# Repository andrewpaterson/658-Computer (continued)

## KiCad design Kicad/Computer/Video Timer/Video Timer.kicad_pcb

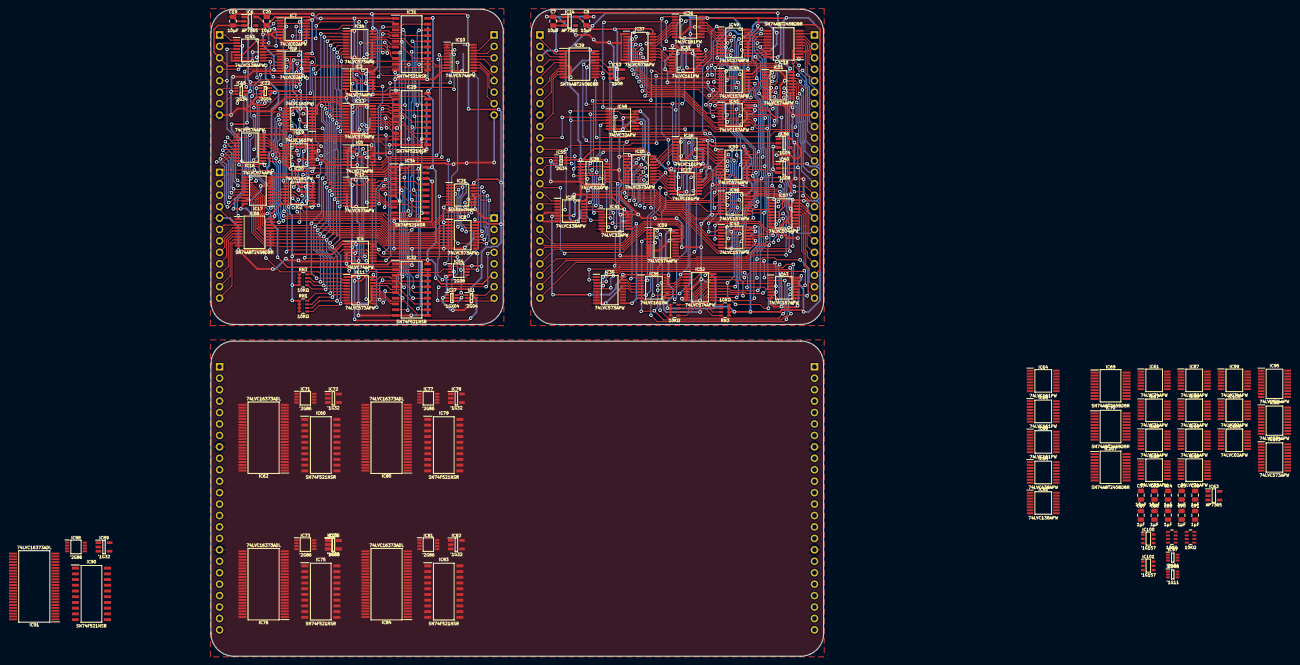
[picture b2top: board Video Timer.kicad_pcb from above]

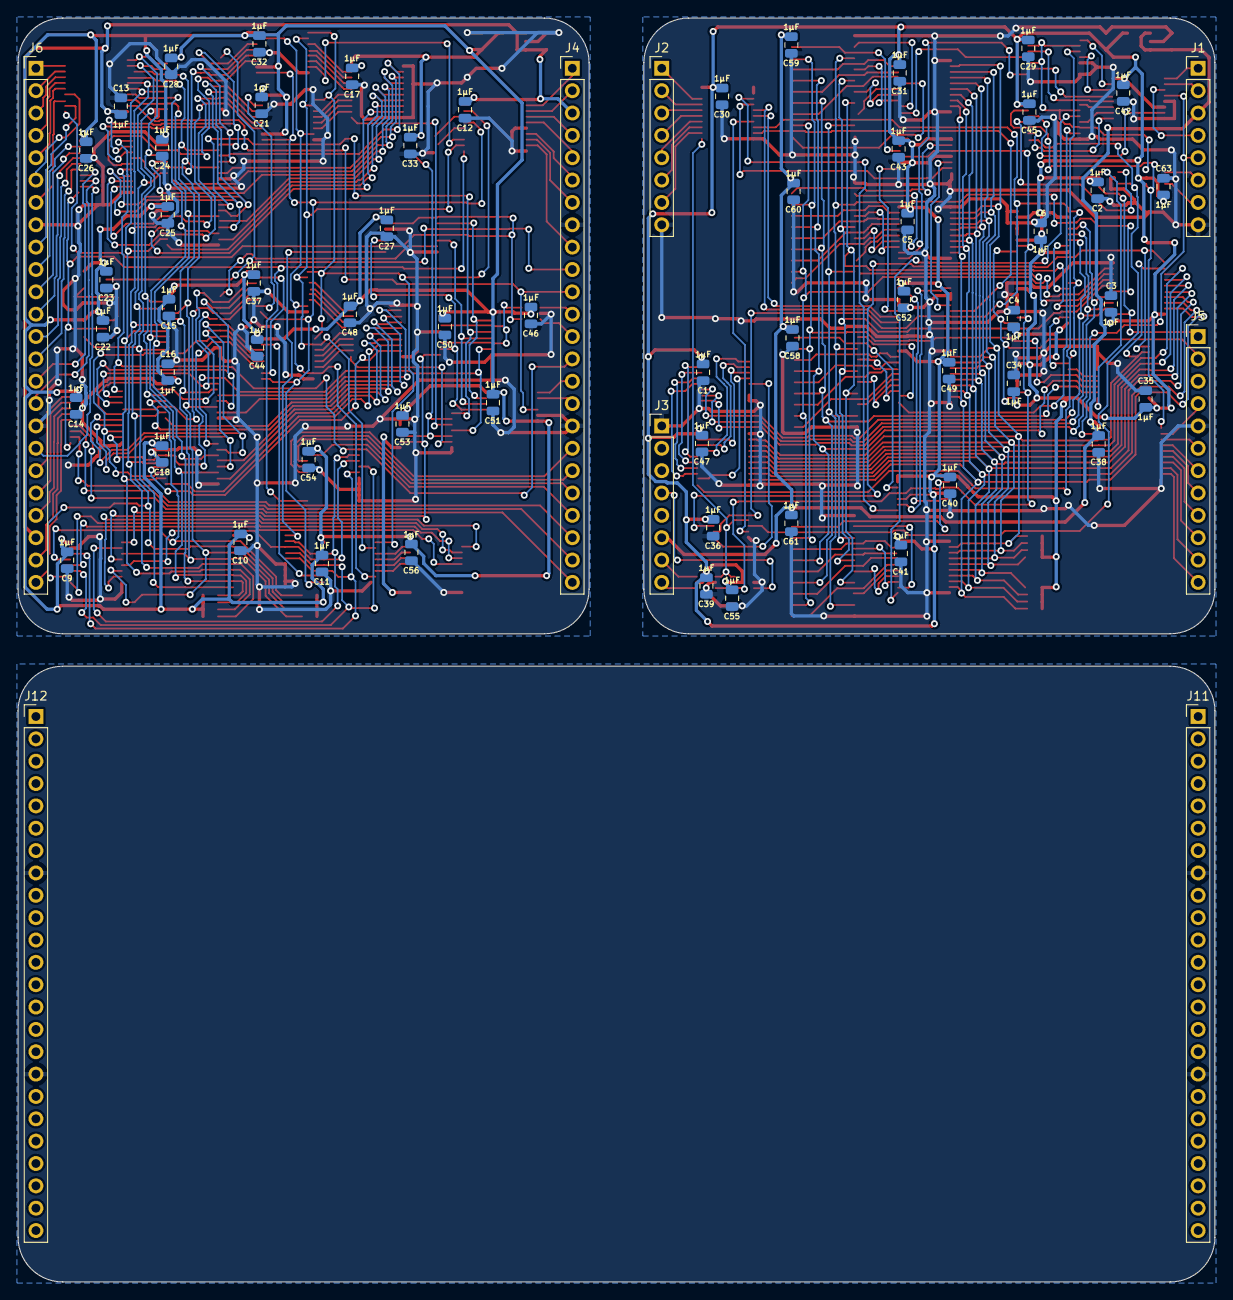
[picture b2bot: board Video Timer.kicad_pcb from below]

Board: 2 copper layers, 136.0 x 143.6 mm, 192 parts (65 on the bottom side), 433 nets.

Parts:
C1, C2, C3, C4, C5, C6, C9, C10, C11, C12, C13, C14, C15, C16, C17, C18, C21, C22, C23, C24, C25, C26, C27, C28, C29, C30, C31, C32, C33, C34, C35, C36, C37, C38, C39, C40, C41, C42, C43, C44, C45, C46, C47, C48, C49, C50, C51, C52, C53, C54, C55, C56, C58, C59, C60, C61, C63, C64, C65, C66, C67, C68, C69, C70, C71: 1μF; C_0805
C7, C8, C19, C20, C57, C62: 10µF; C_0805
IC1, IC22, IC97: 74LVC2G04GW-Q100H; SOP65P210X110-6N
IC2, IC19, IC20, IC23, IC26, IC33, IC35, IC36, IC64, IC65, IC66: 74LVC161PW,112; SOP65P640X110-16N
IC3, IC4, IC5, IC61, IC67, IC68, IC93, IC94, IC98, IC99: 74LVC74APW,118; SOP65P640X110-14N
IC6, IC24, IC63: AP7365-33WG-7; SOT95P285X130-5N
IC7, IC9, IC38, IC86, IC87, IC103, IC104: 74LVC02APW,118; SOP65P640X110-14N
IC8, IC11, IC12, IC13, IC14, IC25, IC30, IC37, IC102: 74LVC573APW,118; SOP65P640X110-20N
IC10, IC16, IC17, IC49, IC50, IC51, IC52, IC57, IC59, IC95, IC96: 74LVC574APW,118; SOP65P640X110-20N
IC15, IC55: 74LVC2G34GW,125; 74LVC2G34GW125
IC18, IC39, IC58, IC69, IC70, IC107: SN74ABT245BDBR; SOP65P780X200-20N
IC21: PI3B3251QE; SOP64P599X175-16N
IC27: 74LVC1GX04GW,125; SOP65P210X110-6N
IC28, IC42, IC85, IC92: 74LVC138APW-Q100J; SOP65P640X110-16N
IC29, IC31, IC32, IC34, IC60, IC75, IC79, IC83, IC90: SN74F521NSR; SOIC127P780X200-20N
IC40, IC53: 74LVC1G08GV,125; SOT95P275X110-5N
IC41, IC48: 74LVC32APW,118; SOP65P640X110-14N
IC43, IC44, IC45, IC46, IC47: 74LVC157APW,118; SOP65P640X110-16N
IC54: 74LVC2G08DP-Q100H; SOP65P400X110-8N
IC56, IC105: 74LVC1G04GV,125; SOT95P275X110-5N
IC62, IC76, IC80, IC84, IC91: 74LVC16373ADL,118; SOP64P1025X280-48N
IC71, IC73, IC77, IC81, IC88: 74LVC2G86DP,125; SOP65P400X110-8N
IC72, IC74, IC78, IC82, IC89: 74LVC1G32GV,125; SOT95P275X110-5N
IC100, IC101: 74LVC1G157GV,125; 74LVC1G157GV125
IC106: 74LVC1G11GW-Q100H; SOP65P210X110-6N
J1, J2, J3: Conn_01x08_Pin; PinHeader_1x08_P2.54mm_Vertical
J4, J6, J11, J12: Conn_01x24_Pin; PinHeader_1x24_P2.54mm_Vertical
J5: Conn_01x12_Pin; PinHeader_1x12_P2.54mm_Vertical
RN1, RN2, RN3, RN4, RN5, RN6: CAY16-103J4LF; CAY16-J4

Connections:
/Address Position/3.3V: C8.1, C9.1, C10.1, C11.1, C14.1, C15.1, C16.1, C17.1, C18.1, C21.1, C22.1, C23.1, C24.1, C25.1, C26.1, C27.1, C28.1, C32.1, C33.1, C37.1, C44.1, C46.1, C48.1, C50.1, C51.1, C53.1, C54.1, C56.1, IC23.16 (3V), IC24.5 (VOUT), IC25.20 (3V), IC26.16 (3V), IC28.6 (E3), IC28.16 (3V), IC30.20 (3V), IC33.10 (CET), IC33.16 (3V), IC35.16 (3V), IC36.10 (CET), IC36.16 (3V), IC37.20 (3V), IC38.14 (3V), IC40.5 (3V), IC41.14 (3V), IC43.16 (3V), IC44.16 (3V), IC45.16 (3V), IC46.16 (3V), IC47.16 (3V), IC48.14 (3V), IC49.20 (3V), IC50.20 (3V), IC51.20 (3V), IC52.20 (3V), IC53.5 (3V), IC55.5 (3V), IC56.5 (3V), IC57.20 (3V), IC59.20 (3V), RN3.5 (R4), RN3.6 (R3), RN3.7 (R2), RN3.8 (R1), RN4.5 (R4), RN4.6 (R3), RN4.7 (R2), RN4.8 (R1)
/Address Position/5V: C7.1, C12.1, C13.1, IC18.20 (5V), IC24.1 (VIN), IC24.3 (EN), IC39.1 (DIR), IC39.20 (5V), J4.3, J6.22
/Address Position/A0: IC28.1 (A0), J4.15
/Address Position/A1: IC28.2 (A1), J4.16
/Address Position/Address Bank ~CS: IC28.13 (~Y2), IC38.9 (3A), IC48.10 (3B)
/Address Position/Address High ~CS: IC28.14 (~Y1), IC38.4 (2A), IC48.5 (2B)
/Address Position/Address Low ~CS: IC28.15 (~Y0), IC38.1 (1A), IC48.2 (1B)
/Address Position/Advance Pixel: IC36.7 (CEP), IC39.13 (B6)
/Address Position/Advance Pixel _{IN}: IC39.7 (A6), J4.6
/Address Position/Advance Row: IC39.17 (B2), IC53.1 (B)
/Address Position/Advance Row _{IN}: IC39.3 (A2), J4.2
/Address Position/C0: IC36.14 (Q0), IC44.2 (1I0), IC49.2 (D0), IC51.2 (D0)
/Address Position/C1: IC36.13 (Q1), IC44.5 (2I0), IC49.3 (D1), IC51.3 (D1)
/Address Position/C2: IC36.12 (Q2), IC44.11 (3I0), IC49.4 (D2), IC51.4 (D2)
/Address Position/C3: IC36.11 (Q3), IC44.14 (4I0), IC49.5 (D3), IC51.5 (D3)
/Address Position/C4: IC33.14 (Q0), IC45.2 (1I0), IC49.6 (D4), IC51.6 (D4)
/Address Position/C5: IC33.13 (Q1), IC45.5 (2I0), IC49.7 (D5), IC51.7 (D5)
/Address Position/C6: IC33.12 (Q2), IC45.11 (3I0), IC49.8 (D6), IC51.8 (D6)
/Address Position/C7: IC33.11 (Q3), IC45.14 (4I0), IC49.9 (D7), IC51.9 (D7)
/Address Position/C8: IC26.14 (Q0), IC46.2 (1I0), IC50.2 (D0), IC57.2 (D0)
/Address Position/C9: IC26.13 (Q1), IC46.5 (2I0), IC50.3 (D1), IC57.3 (D1)
/Address Position/C10: IC26.12 (Q2), IC46.11 (3I0), IC50.4 (D2), IC57.4 (D2)
/Address Position/C11: IC26.11 (Q3), IC46.14 (4I0), IC50.5 (D3), IC57.5 (D3)
/Address Position/C12: IC23.14 (Q0), IC43.2 (1I0), IC50.6 (D4), IC57.6 (D4)
/Address Position/C13: IC23.13 (Q1), IC43.5 (2I0), IC50.7 (D5), IC57.7 (D5)
/Address Position/C14: IC23.12 (Q2), IC43.11 (3I0), IC50.8 (D6), IC57.8 (D6)
/Address Position/C15: IC23.11 (Q3), IC43.14 (4I0), IC50.9 (D7), IC57.9 (D7)
/Address Position/C16: IC35.14 (Q0), IC47.2 (1I0), IC52.2 (D0), IC59.2 (D0)
/Address Position/C17: IC35.13 (Q1), IC47.5 (2I0), IC52.3 (D1), IC59.3 (D1)
/Address Position/C18: IC35.12 (Q2), IC47.11 (3I0), IC52.4 (D2), IC59.4 (D2)
/Address Position/C19: IC35.11 (Q3), IC47.14 (4I0), IC52.5 (D3), IC59.5 (D3)
/Address Position/D0: IC18.11 (B8), IC44.13 (4I1), IC46.13 (4I1), IC47.13 (4I1), IC49.19 (Q0), IC50.19 (Q0), IC52.19 (Q0), RN4.4 (R4)
/Address Position/D0_{IN/OUT}: IC18.9 (A8), J6.1
/Address Position/D1: IC18.12 (B7), IC44.10 (3I1), IC46.10 (3I1), IC47.10 (3I1), IC49.18 (Q1), IC50.18 (Q1), IC52.18 (Q1), RN4.3 (R3)
/Address Position/D1_{IN/OUT}: IC18.8 (A7), J6.2
/Address Position/D2: IC18.13 (B6), IC44.6 (2I1), IC46.6 (2I1), IC47.6 (2I1), IC49.17 (Q2), IC50.17 (Q2), IC52.17 (Q2), RN4.2 (R2)
/Address Position/D2_{IN/OUT}: IC18.7 (A6), J6.3
/Address Position/D3: IC18.14 (B5), IC44.3 (1I1), IC46.3 (1I1), IC47.3 (1I1), IC49.16 (Q3), IC50.16 (Q3), IC52.16 (Q3), RN4.1 (R1)
/Address Position/D3_{IN/OUT}: IC18.6 (A5), J6.4
/Address Position/D4: IC18.15 (B4), IC43.13 (4I1), IC45.13 (4I1), IC49.15 (Q4), IC50.15 (Q4), IC52.15 (Q4), RN3.4 (R4)
/Address Position/D4_{IN/OUT}: IC18.5 (A4), J6.5
/Address Position/D5: IC18.16 (B3), IC43.10 (3I1), IC45.10 (3I1), IC49.14 (Q5), IC50.14 (Q5), IC52.14 (Q5), RN3.3 (R3)
/Address Position/D5_{IN/OUT}: IC18.4 (A3), J6.6
/Address Position/D6: IC18.17 (B2), IC43.6 (2I1), IC45.6 (2I1), IC49.13 (Q6), IC50.13 (Q6), IC52.13 (Q6), RN3.2 (R2)
/Address Position/D6_{IN/OUT}: IC18.3 (A2), J6.7
/Address Position/D7: IC18.18 (B1), IC43.3 (1I1), IC45.3 (1I1), IC49.12 (Q7), IC50.12 (Q7), IC52.12 (Q7), RN3.1 (R1)
/Address Position/D7_{IN/OUT}: IC18.2 (A1), J6.9
/Address Position/Device ~CS: IC18.19 (~OE), IC28.4 (~E1), J4.11
/Address Position/GA0: IC51.19 (Q0), J6.10
/Address Position/GA1: IC51.18 (Q1), J6.11
/Address Position/GA2: IC51.17 (Q2), J6.12
/Address Position/GA3: IC51.16 (Q3), J6.13
/Address Position/GA4: IC51.15 (Q4), J6.14
/Address Position/GA5: IC51.14 (Q5), J6.15
/Address Position/GA6: IC51.13 (Q6), J6.16
/Address Position/GA7: IC51.12 (Q7), J6.18
/Address Position/GA8: IC57.19 (Q0), J6.19
/Address Position/GA9: IC57.18 (Q1), J6.20
/Address Position/GA10: IC57.17 (Q2), J6.21
/Address Position/GA11: IC57.16 (Q3), J6.23
/Address Position/GA12: IC57.15 (Q4), J6.24
/Address Position/GA13: IC57.14 (Q5), J4.24
/Address Position/GA14: IC57.13 (Q6), J4.23
/Address Position/GA15: IC57.12 (Q7), J4.22
/Address Position/GA16: IC59.19 (Q0), J4.21
/Address Position/GA17: IC59.18 (Q1), J4.20
/Address Position/GA18: IC59.17 (Q2), J4.19
/Address Position/GA19: IC59.16 (Q3), J4.18
/Address Position/GND: C7.2, C8.2, C9.2, C10.2, C11.2, C12.2, C13.2, C14.2, C15.2, C16.2, C17.2, C18.2, C21.2, C22.2, C23.2, C24.2, C25.2, C26.2, C27.2, C28.2, C32.2, C33.2, C37.2, C44.2, C46.2, C48.2, C50.2, C51.2, C53.2, C54.2, C56.2, IC18.10 (GND), IC23.8 (GND), IC24.2 (GND), IC25.1 (~OE), IC25.10 (GND), IC26.8 (GND), IC28.3 (A2), IC28.5 (~E2), IC28.8 (GND), IC30.1 (~OE), IC30.6 (D4), IC30.7 (D5), IC30.8 (D6), IC30.9 (D7), IC30.10 (GND), IC33.8 (GND), IC35.8 (GND), IC36.8 (GND), IC37.1 (~OE), IC37.10 (GND), IC38.7 (GND), IC38.12 (4A), IC39.6 (A5), IC39.10 (GND), IC39.19 (~OE), IC40.3 (GND), IC41.7 (GND), IC41.12 (4A), IC41.13 (4B), IC43.8 (GND), IC43.15 (~E), IC44.8 (GND), IC44.15 (~E), IC45.8 (GND), IC45.15 (~E), IC46.8 (GND), IC46.15 (~E), IC47.8 (GND), IC47.15 (~E), IC48.7 (GND), IC48.12 (4A), IC49.10 (GND), IC50.10 (GND), IC51.10 (GND), IC52.6 (D4), IC52.7 (D5), IC52.8 (D6), IC52.9 (D7), IC52.10 (GND), IC53.3 (GND), IC55.2 (GND), IC56.3 (GND), IC57.10 (GND), IC59.6 (D4), IC59.7 (D5), IC59.8 (D6), IC59.9 (D7), IC59.10 (GND), J4.8, J4.17, J6.8, J6.17
/Address Position/Graphics Address ~OE: IC51.1 (~OE), IC57.1 (~OE), IC59.1 (~OE), J4.14
/Address Position/L0: IC37.2 (D0), IC44.4 (1Y)
/Address Position/L1: IC37.3 (D1), IC44.7 (2Y)
/Address Position/L2: IC37.4 (D2), IC44.9 (3Y)
/Address Position/L3: IC37.5 (D3), IC44.12 (4Y)
/Address Position/L4: IC37.6 (D4), IC45.4 (1Y)
/Address Position/L5: IC37.7 (D5), IC45.7 (2Y)
/Address Position/L6: IC37.8 (D6), IC45.9 (3Y)
/Address Position/L7: IC37.9 (D7), IC45.12 (4Y)
/Address Position/L8: IC25.2 (D0), IC46.4 (1Y)
/Address Position/L9: IC25.3 (D1), IC46.7 (2Y)
/Address Position/L10: IC25.4 (D2), IC46.9 (3Y)
/Address Position/L11: IC25.5 (D3), IC46.12 (4Y)
/Address Position/L12: IC25.6 (D4), IC43.4 (1Y)
/Address Position/L13: IC25.7 (D5), IC43.7 (2Y)
/Address Position/L14: IC25.8 (D6), IC43.9 (3Y)
/Address Position/L15: IC25.9 (D7), IC43.12 (4Y)
/Address Position/L16: IC30.2 (D0), IC47.4 (1Y)
/Address Position/L17: IC30.3 (D1), IC47.7 (2Y)
/Address Position/L18: IC30.4 (D2), IC47.9 (3Y)
/Address Position/L19: IC30.5 (D3), IC47.12 (4Y)
/Address Position/LC0: IC36.3 (D0), IC37.19 (Q0)
/Address Position/LC1: IC36.4 (D1), IC37.18 (Q1)
/Address Position/LC2: IC36.5 (D2), IC37.17 (Q2)
/Address Position/LC3: IC36.6 (D3), IC37.16 (Q3)
/Address Position/LC4: IC33.3 (D0), IC37.15 (Q4)
/Address Position/LC5: IC33.4 (D1), IC37.14 (Q5)
/Address Position/LC6: IC33.5 (D2), IC37.13 (Q6)
/Address Position/LC7: IC33.6 (D3), IC37.12 (Q7)
/Address Position/LC8: IC25.19 (Q0), IC26.3 (D0)
/Address Position/LC9: IC25.18 (Q1), IC26.4 (D1)
/Address Position/LC10: IC25.17 (Q2), IC26.5 (D2)
/Address Position/LC11: IC25.16 (Q3), IC26.6 (D3)
/Address Position/LC12: IC23.3 (D0), IC25.15 (Q4)
/Address Position/LC13: IC23.4 (D1), IC25.14 (Q5)
/Address Position/LC14: IC23.5 (D2), IC25.13 (Q6)
/Address Position/LC15: IC23.6 (D3), IC25.12 (Q7)
/Address Position/LC16: IC30.19 (Q0), IC35.3 (D0)
/Address Position/LC17: IC30.18 (Q1), IC35.4 (D1)
/Address Position/LC18: IC30.17 (Q2), IC35.5 (D2)
/Address Position/LC19: IC30.16 (Q3), IC35.6 (D3)
/Address Position/LP·AR: IC41.2 (1B), IC41.5 (2B), IC41.10 (3B), IC53.4 (Y)
/Address Position/Last Pixel + 1: IC39.15 (B4), IC53.2 (A)
/Address Position/Last Pixel + 1 _{IN}: IC39.5 (A4), J4.5
/Address Position/Latch Bank: IC30.11 (LE), IC41.8 (3Y)
/Address Position/Latch High: IC25.11 (LE), IC41.6 (2Y)
/Address Position/Latch Low: IC37.11 (LE), IC41.3 (1Y)
/Address Position/Pixel CLK: IC23.2 (CP), IC26.2 (CP), IC33.2 (CP), IC35.2 (CP), IC36.2 (CP), IC39.12 (B7)
/Address Position/Pixel CLK _{IN}: IC39.8 (A7), J4.7
/Address Position/Read Address Low: IC40.1 (B), IC56.4 (Y)
/Address Position/TC_{0..3}: IC23.7 (CEP), IC26.7 (CEP), IC33.7 (CEP), IC35.7 (CEP), IC36.15 (TC)
/Address Position/TC_{4..7}: IC26.10 (CET), IC33.15 (TC)
/Address Position/TC_{8..11}: IC23.10 (CET), IC26.15 (TC)
/Address Position/TC_{12..15}: IC23.15 (TC), IC35.10 (CET)
/Address Position/Write Address Bank: IC38.8 (3Y), IC41.9 (3A), IC47.1 (S)
/Address Position/Write Address High: IC38.6 (2Y), IC41.4 (2A), IC43.1 (S), IC46.1 (S)
/Address Position/Write Address Low: IC38.3 (1Y), IC41.1 (1A), IC44.1 (S), IC45.1 (S)
/Address Position/~Horizontal Blank: IC23.9 (~PE), IC26.9 (~PE), IC33.9 (~PE), IC35.9 (~PE), IC36.9 (~PE), IC39.16 (B3)
/Address Position/~Horizontal Blank _{IN}: IC39.4 (A3), J4.4
/Address Position/~PC·RAL: IC40.4 (Y), IC49.11 (CP), IC50.11 (CP), IC52.11 (CP)
/Address Position/~Pixel CLK: IC39.11 (B8), IC40.2 (A), IC51.11 (CP), IC57.11 (CP), IC59.11 (CP)
/Address Position/~Pixel CLK _{IN}: IC39.9 (A8), J4.9
/Address Position/~RD: IC18.1 (DIR), IC48.1 (1A), IC48.4 (2A), IC48.9 (3A), IC48.13 (4B), IC55.4 (2Y)
/Address Position/~RD_{IN}: IC55.3 (2A), J4.13
/Address Position/~Read Address Bank: IC48.8 (3Y), IC52.1 (~OE)
/Address Position/~Read Address High: IC48.6 (2Y), IC50.1 (~OE)
/Address Position/~Read Address Low: IC48.3 (1Y), IC49.1 (~OE), IC56.2 (A), J4.10
/Address Position/~Reset: IC23.1 (~MR), IC26.1 (~MR), IC33.1 (~MR), IC35.1 (~MR), IC36.1 (~MR), IC39.18 (B1)
/Address Position/~Reset _{IN}: IC39.2 (A1), J4.1
/Address Position/~WD: IC38.2 (1B), IC38.5 (2B), IC38.10 (3B), IC38.13 (4B), IC55.6 (1Y)
/Address Position/~WD_{IN}: IC55.1 (1A), J4.12
/Horizontal Position/3.3V: C1.1, C2.1, C3.1, C4.1, C5.1, C6.1, C20.1, C29.1, C30.1, C31.1, C34.1, C35.1, C36.1, C39.1, C40.1, C41.1, C42.1, C43.1, C45.1, C47.1, C49.1, C52.1, C55.1, C63.1, IC1.5 (3V), IC2.7 (CEP), IC2.16 (3V), IC3.1 (~1RD), IC3.4 (~1SD), IC3.10 (~2SD), IC3.13 (~2RD), IC3.14 (3V), IC4.1 (~1RD), IC4.4 (~1SD), IC4.10 (~2SD), IC4.13 (~2RD), IC4.14 (3V), IC5.14 (3V), IC6.5 (VOUT), IC7.14 (3V), IC8.20 (3V), IC9.14 (3V), IC10.20 (3V), IC11.20 (3V), IC12.20 (3V), IC13.20 (3V), IC14.20 (3V), IC15.5 (3V), IC16.20 (3V), IC17.20 (3V), IC19.3 (D0), IC19.7 (CEP), IC19.10 (CET), IC19.16 (3V), IC20.7 (CEP), IC20.16 (3V), IC21.16 (3V), IC22.5 (3V), IC27.5 (3V), IC42.6 (E3), IC42.16 (3V), IC54.8 (3V), RN1.5 (R4), RN1.6 (R3), RN1.7 (R2), RN1.8 (R1), RN2.5 (R4), RN2.6 (R3), RN2.7 (R2), RN2.8 (R1)
/Horizontal Position/5V: C19.1, C38.1, C58.1, C59.1, C60.1, C61.1, IC6.1 (VIN), IC6.3 (EN), IC29.20 (5V), IC31.20 (5V), IC32.20 (5V), IC34.20 (5V), IC58.20 (5V), J1.3, J3.6
/Horizontal Position/A0: IC42.1 (A0), J1.1
/Horizontal Position/A1: IC42.2 (A1), J1.2
/Horizontal Position/A2: IC42.3 (A2), J1.4
/Horizontal Position/Advance Pixel: IC10.7 (D5), IC54.3 (2Y)
/Horizontal Position/Advance Pixel _{OUT}: IC10.14 (Q5), J2.5
/Horizontal Position/Back Porch End D0: IC12.12 (Q7), IC34.2 (P0)
/Horizontal Position/Back Porch End D1: IC12.13 (Q6), IC34.4 (P1)
/Horizontal Position/Back Porch End D2: IC12.14 (Q5), IC34.6 (P2)
/Horizontal Position/Back Porch End D3: IC12.15 (Q4), IC34.8 (P3)
/Horizontal Position/Back Porch End D4: IC12.16 (Q3), IC34.11 (P4)
/Horizontal Position/Back Porch End D5: IC12.17 (Q2), IC34.13 (P5)
/Horizontal Position/Back Porch End D6: IC12.18 (Q1), IC34.15 (P6)
/Horizontal Position/Back Porch End D7: IC12.19 (Q0), IC34.17 (P7)
/Horizontal Position/Back Porch Start D0: IC11.12 (Q7), IC32.2 (P0)
/Horizontal Position/Back Porch Start D1: IC11.13 (Q6), IC32.4 (P1)
/Horizontal Position/Back Porch Start D2: IC11.14 (Q5), IC32.6 (P2)
/Horizontal Position/Back Porch Start D3: IC11.15 (Q4), IC32.8 (P3)
/Horizontal Position/Back Porch Start D4: IC11.16 (Q3), IC32.11 (P4)
/Horizontal Position/Back Porch Start D5: IC11.17 (Q2), IC32.13 (P5)
/Horizontal Position/Back Porch Start D6: IC11.18 (Q1), IC32.15 (P6)
/Horizontal Position/Back Porch Start D7: IC11.19 (Q0), IC32.17 (P7)
/Horizontal Position/Clock Read Row Position: IC16.11 (CP), IC17.11 (CP), IC54.7 (1Y)
/Horizontal Position/D0: IC8.9 (D7), IC11.9 (D7), IC12.9 (D7), IC13.9 (D7), IC14.9 (D7), IC16.19 (Q0), IC17.19 (Q0), IC58.11 (B8), RN1.1 (R1)
/Horizontal Position/D0_{IN/OUT}: IC58.9 (A8), J5.12
/Horizontal Position/D1: IC8.8 (D6), IC11.8 (D6), IC12.8 (D6), IC13.8 (D6), IC14.8 (D6), IC16.18 (Q1), IC17.18 (Q1), IC58.12 (B7), RN1.2 (R2)
/Horizontal Position/D1_{IN/OUT}: IC58.8 (A7), J5.11
/Horizontal Position/D2: IC8.7 (D5), IC11.7 (D5), IC12.7 (D5), IC13.7 (D5), IC14.7 (D5), IC16.17 (Q2), IC17.17 (Q2), IC58.13 (B6), RN1.3 (R3)
/Horizontal Position/D2_{IN/OUT}: IC58.7 (A6), J5.10
/Horizontal Position/D3: IC8.6 (D4), IC11.6 (D4), IC12.6 (D4), IC13.6 (D4), IC14.6 (D4), IC16.16 (Q3), IC17.16 (Q3), IC58.14 (B5), RN1.4 (R4)
/Horizontal Position/D3_{IN/OUT}: IC58.6 (A5), J5.9
/Horizontal Position/D4: IC8.5 (D3), IC11.5 (D3), IC12.5 (D3), IC13.5 (D3), IC14.5 (D3), IC16.15 (Q4), IC17.15 (Q4), IC58.15 (B4), RN2.1 (R1)
/Horizontal Position/D4_{IN/OUT}: IC58.5 (A4), J5.8
/Horizontal Position/D5: IC8.4 (D2), IC11.4 (D2), IC12.4 (D2), IC13.4 (D2), IC14.4 (D2), IC16.14 (Q5), IC17.14 (Q5), IC58.16 (B3), RN2.2 (R2)
/Horizontal Position/D5_{IN/OUT}: IC58.4 (A3), J5.7
/Horizontal Position/D6: IC8.3 (D1), IC11.3 (D1), IC12.3 (D1), IC13.3 (D1), IC14.3 (D1), IC16.13 (Q6), IC17.13 (Q6), IC58.17 (B2), RN2.3 (R3)
/Horizontal Position/D6_{IN/OUT}: IC58.3 (A2), J5.6
/Horizontal Position/D7: IC8.2 (D0), IC11.2 (D0), IC12.2 (D0), IC13.2 (D0), IC14.2 (D0), IC16.12 (Q7), IC17.12 (Q7), IC58.18 (B1), RN2.4 (R4)
/Horizontal Position/D7_{IN/OUT}: IC58.2 (A1), J5.4
/Horizontal Position/Device ~CS: IC42.4 (~E1), IC58.19 (~OE), J1.5
/Horizontal Position/First Pixel: IC4.8 (~2Q), IC10.3 (D1)
/Horizontal Position/First Pixel _{OUT}: IC10.18 (Q1), J2.1
/Horizontal Position/Front Porch Start D0: IC13.12 (Q7), IC29.2 (P0)
/Horizontal Position/Front Porch Start D1: IC13.13 (Q6), IC29.4 (P1)
/Horizontal Position/Front Porch Start D2: IC13.14 (Q5), IC29.6 (P2)
/Horizontal Position/Front Porch Start D3: IC13.15 (Q4), IC29.8 (P3)
/Horizontal Position/Front Porch Start D4: IC13.16 (Q3), IC29.11 (P4)
/Horizontal Position/Front Porch Start D5: IC13.17 (Q2), IC29.13 (P5)
/Horizontal Position/Front Porch Start D6: IC13.18 (Q1), IC29.15 (P6)
/Horizontal Position/Front Porch Start D7: IC13.19 (Q0), IC29.17 (P7)
/Horizontal Position/GND: C1.2, C2.2, C3.2, C4.2, C5.2, C6.2, C19.2, C20.2, C29.2, C30.2, C31.2, C34.2, C35.2, C36.2, C38.2, C39.2, C40.2, C41.2, C42.2, C43.2, C45.2, C47.2, C49.2, C52.2, C55.2, C58.2, C59.2, C60.2, C61.2, C63.2, IC1.2 (GND), IC2.3 (D0), IC2.4 (D1), IC2.5 (D2), IC2.6 (D3), IC2.8 (GND), IC3.7 (GND), IC4.7 (GND), IC5.2 (1D), IC5.3 (1CP), IC5.7 (GND), IC5.11 (2CP), IC5.12 (2D), IC6.2 (GND), IC7.5 (2B), IC7.7 (GND), IC8.1 (~OE), IC8.10 (GND), IC9.7 (GND), IC10.1 (~OE), IC10.2 (D0), IC10.10 (GND), IC11.1 (~OE), IC11.10 (GND), IC12.1 (~OE), IC12.10 (GND), IC13.1 (~OE), IC13.10 (GND), IC14.1 (~OE), IC14.10 (GND), IC15.2 (GND), IC16.10 (GND), IC17.6 (D4), IC17.7 (D5), IC17.8 (D6), IC17.9 (D7), IC17.10 (GND), IC19.4 (D1), IC19.5 (D2), IC19.6 (D3), IC19.8 (GND), IC20.3 (D0), IC20.4 (D1), IC20.5 (D2), IC20.6 (D3), IC20.8 (GND), IC21.7 (~OE), IC21.8 (GND), IC22.2 (GND), IC27.2 (GND), IC29.1 (~OE), IC29.10 (GND), IC31.1 (~OE), IC31.10 (GND), IC32.1 (~OE), IC32.10 (GND), IC34.1 (~OE), IC34.10 (GND), IC42.5 (~E2), IC42.8 (GND), IC54.4 (GND), IC58.10 (GND), J1.8, J2.8, J3.1, J5.5
/Horizontal Position/Horizontal Blank: IC5.5 (1Q), IC10.9 (D7)
/Horizontal Position/Horizontal Blank _{OUT}: IC10.12 (Q7), J2.7
/Horizontal Position/Horizontal Sync: IC5.9 (2Q), IC10.6 (D4)
/Horizontal Position/Horizontal Sync _{OUT}: IC10.15 (Q4), J2.4
/Horizontal Position/Last Pixel + 1: IC3.6 (~1Q), IC10.4 (D2)
/Horizontal Position/Last Pixel + 1 _{OUT}: IC10.17 (Q2), J2.2
/Horizontal Position/Pixel CLK: IC1.3 (2A), IC2.2 (CP), IC3.3 (1CP), IC3.11 (2CP), IC4.3 (1CP), IC4.11 (2CP), IC19.2 (CP), IC20.2 (CP), IC27.4 (~Y)
/Horizontal Position/Pixel CLK _{IN}: IC27.3 (X1), J3.4
/Horizontal Position/Pixel CLK _{OUT}: IC1.6 (1Y), J3.7
/Horizontal Position/R0: IC16.2 (D0), IC19.14 (Q0), IC21.11 (S0)
/Horizontal Position/R1: IC16.3 (D1), IC19.13 (Q1), IC21.10 (S1)
/Horizontal Position/R2: IC16.4 (D2), IC19.12 (Q2), IC21.9 (S2)
/Horizontal Position/R3: IC16.5 (D3), IC19.11 (Q3), IC29.3 (Q0), IC31.3 (Q0), IC32.3 (Q0), IC34.3 (Q0)
/Horizontal Position/R4: IC16.6 (D4), IC20.14 (Q0), IC29.5 (Q1), IC31.5 (Q1), IC32.5 (Q1), IC34.5 (Q1)
/Horizontal Position/R5: IC16.7 (D5), IC20.13 (Q1), IC29.7 (Q2), IC31.7 (Q2), IC32.7 (Q2), IC34.7 (Q2)
/Horizontal Position/R6: IC16.8 (D6), IC20.12 (Q2), IC29.9 (Q3), IC31.9 (Q3), IC32.9 (Q3), IC34.9 (Q3)
/Horizontal Position/R7: IC16.9 (D7), IC20.11 (Q3), IC29.12 (Q4), IC31.12 (Q4), IC32.12 (Q4), IC34.12 (Q4)
/Horizontal Position/R8: IC2.14 (Q0), IC17.2 (D0), IC29.14 (Q5), IC31.14 (Q5), IC32.14 (Q5), IC34.14 (Q5)
/Horizontal Position/R9: IC2.13 (Q1), IC17.3 (D1), IC29.16 (Q6), IC31.16 (Q6), IC32.16 (Q6), IC34.16 (Q6)
/Horizontal Position/R10: IC2.12 (Q2), IC17.4 (D2), IC29.18 (Q7), IC31.18 (Q7), IC32.18 (Q7), IC34.18 (Q7)
/Horizontal Position/R11: IC2.11 (Q3), IC17.5 (D3)
/Horizontal Position/RPS0: IC8.19 (Q0), IC21.3 (I1)
/Horizontal Position/RPS1: IC8.18 (Q1), IC21.2 (I2)
/Horizontal Position/RPS2: IC8.17 (Q2), IC21.1 (I3)
/Horizontal Position/RPS3: IC8.16 (Q3), IC21.15 (I4)
/Horizontal Position/RPS4: IC8.15 (Q4), IC21.14 (I5)
/Horizontal Position/RPS5: IC8.14 (Q5), IC21.13 (I6)
/Horizontal Position/RPS6: IC8.13 (Q6), IC21.12 (I7)
/Horizontal Position/RPS7: IC8.12 (Q7), IC21.4 (I0)
/Horizontal Position/Read Row Position High: IC9.11 (4Y), IC22.1 (1A)
/Horizontal Position/Read Row Position High ~CS: IC9.12 (4A), IC42.7 (~Y7)
/Horizontal Position/Read Row Position Low: IC9.8 (3Y), IC22.3 (2A), IC54.2 (1B)
/Horizontal Position/Read Row Position Low ~CS: IC9.9 (3A), IC42.9 (~Y6)
/Horizontal Position/Select Advance Pixel: IC21.5 (Y), IC54.5 (2A)
/Horizontal Position/Sync Start D0: IC14.12 (Q7), IC31.2 (P0)
/Horizontal Position/Sync Start D1: IC14.13 (Q6), IC31.4 (P1)
/Horizontal Position/Sync Start D2: IC14.14 (Q5), IC31.6 (P2)
/Horizontal Position/Sync Start D3: IC14.15 (Q4), IC31.8 (P3)
/Horizontal Position/Sync Start D4: IC14.16 (Q3), IC31.11 (P4)
/Horizontal Position/Sync Start D5: IC14.17 (Q2), IC31.13 (P5)
/Horizontal Position/Sync Start D6: IC14.18 (Q1), IC31.15 (P6)
/Horizontal Position/Sync Start D7: IC14.19 (Q0), IC31.17 (P7)
/Horizontal Position/TC_{0123}: IC19.15 (TC), IC20.10 (CET)
/Horizontal Position/TC_{4567}: IC2.10 (CET), IC20.15 (TC)
/Horizontal Position/Write Back Porch End: IC9.6 (2Y), IC12.11 (LE)
/Horizontal Position/Write Back Porch End ~CS: IC9.4 (2A), IC42.10 (~Y5)
/Horizontal Position/Write Back Porch Start: IC9.3 (1Y), IC11.11 (LE)
/Horizontal Position/Write Back Porch Start ~CS: IC9.1 (1A), IC42.11 (~Y4)
/Horizontal Position/Write Front Porch Start: IC7.8 (3Y), IC13.11 (LE)
/Horizontal Position/Write Front Porch Start ~CS: IC7.9 (3A), IC42.13 (~Y2)
/Horizontal Position/Write Shift Pattern: IC7.3 (1Y), IC8.11 (LE)
/Horizontal Position/Write Shift Pattern ~CS: IC7.1 (1A), IC42.15 (~Y0)
/Horizontal Position/Write Sync Start: IC7.11 (4Y), IC14.11 (LE)
/Horizontal Position/Write Sync Start ~CS: IC7.12 (4A), IC42.12 (~Y3)
/Horizontal Position/~Back Porch End: IC4.9 (2Q), IC5.1 (~1RD)
/Horizontal Position/~Back Porch End _{CMP}: IC4.12 (2D), IC34.19 (~P=Q)
/Horizontal Position/~Back Porch Start: IC4.5 (1Q), IC5.13 (~2RD)
/Horizontal Position/~Back Porch Start _{CMP}: IC4.2 (1D), IC32.19 (~P=Q)
/Horizontal Position/~Front Porch Start: IC3.5 (1Q), IC5.4 (~1SD)
/Horizontal Position/~Front Porch Start _{CMP}: IC3.2 (1D), IC29.19 (~P=Q)
/Horizontal Position/~Horizontal Blank: IC2.9 (~PE), IC5.6 (~1Q), IC10.8 (D6), IC19.9 (~PE), IC20.9 (~PE), IC54.6 (2B)
/Horizontal Position/~Horizontal Blank _{OUT}: IC10.13 (Q6), J2.6
/Horizontal Position/~Horizontal Sync: IC5.8 (~2Q), IC10.5 (D3)
/Horizontal Position/~Horizontal Sync _{OUT}: IC10.16 (Q3), J2.3
/Horizontal Position/~Pixel CLK: IC1.1 (1A), IC10.11 (CP), IC27.6 (Y), IC54.1 (1A)
/Horizontal Position/~Pixel CLK _{OUT}: IC1.4 (2Y), J3.8
/Horizontal Position/~RD: IC9.10 (3B), IC9.13 (4B), IC15.4 (2Y), IC58.1 (DIR)
/Horizontal Position/~RD_{IN}: IC15.3 (2A), J1.7
/Horizontal Position/~RRPH: IC17.1 (~OE), IC22.6 (1Y)
/Horizontal Position/~Read Row Position Low: IC16.1 (~OE), IC22.4 (2Y), J5.1
/Horizontal Position/~Reset: IC2.1 (~MR), IC19.1 (~MR), IC20.1 (~MR), J5.2
/Horizontal Position/~Sync Start: IC3.9 (2Q), IC5.10 (~2SD)
/Horizontal Position/~Sync Start _{CMP}: IC3.12 (2D), IC31.19 (~P=Q)
/Horizontal Position/~WD: IC7.2 (1B), IC7.10 (3B), IC7.13 (4B), IC9.2 (1B), IC9.5 (2B), IC15.6 (1Y)
/Horizontal Position/~WD_{IN}: IC15.1 (1A), J1.6
/Horizontal Position/~Y1: IC7.4 (2A), IC42.14 (~Y1)
/Vertical Position/3.3V: C62.1, C64.1, C65.1, C66.1, C67.1, C68.1, C69.1, C71.1, IC61.1 (~1RD), IC61.4 (~1SD), IC61.10 (~2SD), IC61.13 (~2RD), IC61.14 (3V), IC62.7 (3V), IC62.18 (3V), IC62.31 (3V), IC62.42 (3V), IC63.5 (VOUT), IC64.3 (D0), IC64.7 (CEP), IC64.10 (CET), IC64.16 (3V), IC65.7 (CEP), IC65.16 (3V), IC66.7 (CEP), IC66.16 (3V), IC67.1 (~1RD), IC67.4 (~1SD), IC67.10 (~2SD), IC67.13 (~2RD), IC67.14 (3V), IC68.14 (3V), IC71.8 (VCC), IC72.5 (3V), IC73.8 (VCC), IC74.5 (3V), IC76.7 (3V), IC76.18 (3V), IC76.31 (3V), IC76.42 (3V), IC77.8 (VCC), IC78.5 (3V), IC80.7 (3V), IC80.18 (3V), IC80.31 (3V), IC80.42 (3V), IC81.8 (VCC), IC82.5 (3V), IC84.7 (3V), IC84.18 (3V), IC84.31 (3V), IC84.42 (3V), IC85.6 (E3), IC85.16 (3V), IC86.14 (3V), IC87.14 (3V), IC88.8 (VCC), IC89.5 (3V), IC91.7 (3V), IC91.18 (3V), IC91.31 (3V), IC91.42 (3V), IC92.16 (3V), IC93.1 (~1RD), IC93.10 (~2SD), IC93.13 (~2RD), IC93.14 (3V), IC94.4 (~1SD), IC94.10 (~2SD), IC94.14 (3V), IC95.20 (3V), IC96.20 (3V), IC97.5 (3V), IC98.4 (~1SD), IC98.10 (~2SD), IC98.14 (3V), IC99.1 (~1RD), IC99.4 (~1SD), IC99.10 (~2SD), IC99.13 (~2RD), IC99.14 (3V), IC100.5 (3V), IC101.5 (3V), IC102.20 (3V), IC103.14 (3V), IC104.9 (3A), IC104.12 (4A), IC104.14 (3V), IC105.5 (3V), IC106.5 (3V), RN5.5 (R4), RN5.6 (R3), RN5.7 (R2), RN5.8 (R1), RN6.5 (R4), RN6.6 (R3), RN6.7 (R2), RN6.8 (R1)
/Vertical Position/5V: C57.1, C70.1, IC60.20 (5V), IC63.1 (VIN), IC63.3 (EN), IC69.20 (5V), IC70.1 (DIR), IC70.20 (5V), IC75.20 (5V), IC79.20 (5V), IC83.20 (5V), IC90.20 (5V), IC107.1 (DIR), IC107.20 (5V), J11.3, J12.22
/Vertical Position/A0: IC85.1 (A0), IC92.1 (A0), J11.1
/Vertical Position/A1: IC85.2 (A1), IC92.2 (A1), J11.2
/Vertical Position/A2: IC85.3 (A2), IC92.3 (A2), J11.4
/Vertical Position/A3: IC85.5 (~E2), IC92.6 (E3), J11.5
/Vertical Position/Back Porch Start D0: IC79.2 (P0), IC80.2 (1Q0)
/Vertical Position/Back Porch Start D1: IC79.4 (P1), IC80.3 (1Q1)
/Vertical Position/Back Porch Start D2: IC79.6 (P2), IC80.5 (1Q2)
/Vertical Position/Back Porch Start D3: IC79.8 (P3), IC80.6 (1Q3)
/Vertical Position/Back Porch Start D4: IC79.11 (P4), IC80.8 (1Q4)
/Vertical Position/Back Porch Start D5: IC79.13 (P5), IC80.9 (1Q5)
/Vertical Position/Back Porch Start D6: IC79.15 (P6), IC80.11 (1Q6)
/Vertical Position/Back Porch Start D7: IC79.17 (P7), IC80.12 (1Q7)
/Vertical Position/Back Porch Start D8: IC77.2 (1B), IC80.13 (2Q0)
/Vertical Position/Back Porch Start D9: IC77.6 (2B), IC80.14 (2Q1)
/Vertical Position/Clear Interrupt: IC103.8 (3Y), IC105.2 (A)
/Vertical Position/Clear Interrupt ~CS: IC92.13 (~Y2), IC103.9 (3A)
/Vertical Position/D0: IC62.36 (2D0), IC62.47 (1D0), IC69.11 (B8), IC76.36 (2D0), IC76.47 (1D0), IC80.36 (2D0), IC80.47 (1D0), IC84.36 (2D0), IC84.47 (1D0), IC91.36 (2D0), IC91.47 (1D0), IC95.19 (Q0), IC96.19 (Q0), IC102.2 (D0), RN6.1 (R1)
/Vertical Position/D0_{IN/OUT}: IC69.9 (A8), J11.24
/Vertical Position/D1: IC62.35 (2D1), IC62.46 (1D1), IC69.12 (B7), IC76.35 (2D1), IC76.46 (1D1), IC80.35 (2D1), IC80.46 (1D1), IC84.35 (2D1), IC84.46 (1D1), IC91.35 (2D1), IC91.46 (1D1), IC95.18 (Q1), IC96.18 (Q1), IC102.3 (D1), RN6.2 (R2)
/Vertical Position/D1_{IN/OUT}: IC69.8 (A7), J11.23
/Vertical Position/D2: IC62.33 (2D2), IC62.44 (1D2), IC69.13 (B6), IC76.44 (1D2), IC80.33 (2D2), IC80.44 (1D2), IC84.33 (2D2), IC84.44 (1D2), IC91.33 (2D2), IC91.44 (1D2), IC95.17 (Q2), IC96.17 (Q2), IC102.4 (D2), RN6.3 (R3)
/Vertical Position/D2_{IN/OUT}: IC69.7 (A6), J11.22
/Vertical Position/D3: IC62.32 (2D3), IC62.43 (1D3), IC69.14 (B5), IC76.43 (1D3), IC80.32 (2D3), IC80.43 (1D3), IC84.32 (2D3), IC84.43 (1D3), IC91.32 (2D3), IC91.43 (1D3), IC95.16 (Q3), IC96.16 (Q3), RN6.4 (R4)
/Vertical Position/D3_{IN/OUT}: IC69.6 (A5), J11.21
/Vertical Position/D4: IC62.41 (1D4), IC69.15 (B4), IC76.41 (1D4), IC80.41 (1D4), IC84.41 (1D4), IC91.41 (1D4), IC95.15 (Q4), IC96.15 (Q4), RN5.1 (R1)
/Vertical Position/D4_{IN/OUT}: IC69.5 (A4), J11.20
/Vertical Position/D5: IC62.40 (1D5), IC69.16 (B3), IC76.40 (1D5), IC80.40 (1D5), IC84.40 (1D5), IC91.40 (1D5), IC95.14 (Q5), IC96.14 (Q5), RN5.2 (R2)
/Vertical Position/D5_{IN/OUT}: IC69.4 (A3), J11.19
/Vertical Position/D6: IC62.38 (1D6), IC69.17 (B2), IC76.38 (1D6), IC80.38 (1D6), IC84.38 (1D6), IC91.38 (1D6), IC95.13 (Q6), IC96.13 (Q6), RN5.3 (R3)
/Vertical Position/D6_{IN/OUT}: IC69.3 (A2), J11.18
/Vertical Position/D7: IC62.37 (1D7), IC69.18 (B1), IC76.37 (1D7), IC80.37 (1D7), IC84.37 (1D7), IC91.37 (1D7), IC95.12 (Q7), IC96.12 (Q7), RN5.4 (R4)
/Vertical Position/D7_{IN/OUT}: IC69.2 (A1), J11.16
/Vertical Position/Device ~CS: IC69.19 (~OE), IC85.4 (~E1), IC92.4 (~E1), J11.13
/Vertical Position/First Pixel: IC61.3 (1CP), IC61.11 (2CP), IC67.3 (1CP), IC67.11 (2CP), IC70.16 (B3), IC98.5 (1Q)
/Vertical Position/First Pixel _{IN}: IC64.2 (CP), IC65.2 (CP), IC66.2 (CP), IC70.4 (A3), IC98.2 (1D), J11.9
/Vertical Position/Front Porch Start D0: IC75.2 (P0), IC76.2 (1Q0)
/Vertical Position/Front Porch Start D1: IC75.4 (P1), IC76.3 (1Q1)
/Vertical Position/Front Porch Start D2: IC75.6 (P2), IC76.5 (1Q2)
/Vertical Position/Front Porch Start D3: IC75.8 (P3), IC76.6 (1Q3)
/Vertical Position/Front Porch Start D4: IC75.11 (P4), IC76.8 (1Q4)
/Vertical Position/Front Porch Start D5: IC75.13 (P5), IC76.9 (1Q5)
/Vertical Position/Front Porch Start D6: IC75.15 (P6), IC76.11 (1Q6)
/Vertical Position/Front Porch Start D7: IC75.17 (P7), IC76.12 (1Q7)
/Vertical Position/Front Porch Start D8: IC73.2 (1B), IC76.13 (2Q0)
/Vertical Position/Front Porch Start D9: IC73.6 (2B), IC76.14 (2Q1)
/Vertical Position/GND: C57.2, C62.2, C64.2, C65.2, C66.2, C67.2, C68.2, C69.2, C70.2, C71.2, IC60.10 (GND), IC61.7 (GND), IC62.1 (1~OE), IC62.4 (GND), IC62.10 (GND), IC62.15 (GND), IC62.21 (GND), IC62.24 (2~OE), IC62.26 (2D7), IC62.27 (2D6), IC62.28 (GND), IC62.29 (2D5), IC62.30 (2D4), IC62.34 (GND), IC62.39 (GND), IC62.45 (GND), IC63.2 (GND), IC64.4 (D1), IC64.5 (D2), IC64.6 (D3), IC64.8 (GND), IC65.3 (D0), IC65.4 (D1), IC65.5 (D2), IC65.6 (D3), IC65.8 (GND), IC66.3 (D0), IC66.4 (D1), IC66.5 (D2), IC66.6 (D3), IC66.8 (GND), IC67.7 (GND), IC68.2 (1D), IC68.3 (1CP), IC68.7 (GND), IC68.11 (2CP), IC68.12 (2D), IC69.10 (GND), IC70.8 (A7), IC70.9 (A8), IC70.10 (GND), IC70.19 (~OE), IC71.4 (GND), IC72.3 (GND), IC73.4 (GND), IC74.3 (GND), IC75.10 (GND), IC76.1 (1~OE), IC76.4 (GND), IC76.10 (GND), IC76.15 (GND), IC76.21 (GND), IC76.24 (2~OE), IC76.26 (2D7), IC76.27 (2D6), IC76.28 (GND), IC76.29 (2D5), IC76.30 (2D4), IC76.32 (2D3), IC76.33 (2D2), IC76.34 (GND), IC76.39 (GND), IC76.45 (GND), IC77.4 (GND), IC78.3 (GND), IC79.10 (GND), IC80.1 (1~OE), IC80.4 (GND), IC80.10 (GND), IC80.15 (GND), IC80.21 (GND), IC80.24 (2~OE), IC80.26 (2D7), IC80.27 (2D6), IC80.28 (GND), IC80.29 (2D5), IC80.30 (2D4), IC80.34 (GND), IC80.39 (GND), IC80.45 (GND), IC81.4 (GND), IC82.3 (GND), IC83.10 (GND), IC84.1 (1~OE), IC84.4 (GND), IC84.10 (GND), IC84.15 (GND), IC84.21 (GND), IC84.24 (2~OE), IC84.26 (2D7), IC84.27 (2D6), IC84.28 (GND), IC84.29 (2D5), IC84.30 (2D4), IC84.34 (GND), IC84.39 (GND), IC84.45 (GND), IC85.8 (GND), IC86.7 (GND), IC87.7 (GND), IC88.4 (GND), IC89.3 (GND), IC90.10 (GND), IC91.1 (1~OE), IC91.4 (GND), IC91.10 (GND), IC91.15 (GND), IC91.21 (GND), IC91.24 (2~OE), IC91.26 (2D7), IC91.27 (2D6), IC91.28 (GND), IC91.29 (2D5), IC91.30 (2D4), IC91.34 (GND), IC91.39 (GND), IC91.45 (GND), IC92.5 (~E2), IC92.8 (GND), IC93.7 (GND), IC93.11 (2CP), IC93.12 (2D), IC94.7 (GND), IC95.10 (GND), IC96.6 (D4), IC96.7 (D5), IC96.8 (D6), IC96.9 (D7), IC96.10 (GND), IC97.2 (GND), IC98.7 (GND), IC99.7 (GND), IC100.2 (GND), IC101.2 (GND), IC102.1 (~OE), IC102.5 (D3), IC102.6 (D4), IC102.7 (D5), IC102.8 (D6), IC102.9 (D7), IC102.10 (GND), IC103.7 (GND), IC104.7 (GND), IC105.3 (GND), IC106.2 (GND), IC107.2 (A1), IC107.3 (A2), IC107.4 (A3), IC107.10 (GND), IC107.19 (~OE), J11.8, J11.17, J12.8, J12.17
/Vertical Position/Horizontal Blank: IC94.9 (2Q), IC107.9 (A8)
/Vertical Position/Horizontal Blank _{IN}: IC94.12 (2D), J12.2
/Vertical Position/Horizontal Blank _{OUT}: IC107.11 (B8), J12.13
/Vertical Position/Horizontal Sync: IC94.5 (1Q), IC101.1 (I1)
/Vertical Position/Horizontal Sync _{IN}: IC94.2 (1D), J12.1
/Vertical Position/Horizontal Sync _{OUT}: IC107.14 (B5), J12.10
/Vertical Position/Interrupt D0: IC90.2 (P0), IC91.2 (1Q0)
/Vertical Position/Interrupt D1: IC90.4 (P1), IC91.3 (1Q1)
/Vertical Position/Interrupt D2: IC90.6 (P2), IC91.5 (1Q2)
/Vertical Position/Interrupt D3: IC90.8 (P3), IC91.6 (1Q3)
/Vertical Position/Interrupt D4: IC90.11 (P4), IC91.8 (1Q4)
/Vertical Position/Interrupt D5: IC90.13 (P5), IC91.9 (1Q5)
/Vertical Position/Interrupt D6: IC90.15 (P6), IC91.11 (1Q6)
/Vertical Position/Interrupt D7: IC90.17 (P7), IC91.12 (1Q7)
/Vertical Position/Interrupt D8: IC88.2 (1B), IC91.13 (2Q0)
/Vertical Position/Interrupt D9: IC88.6 (2B), IC91.14 (2Q1)
/Vertical Position/Interrupt Enable: IC102.17 (Q2), IC106.3 (B)
/Vertical Position/Last Pixel + 1: IC70.15 (B4), IC93.3 (1CP), IC98.9 (2Q)
/Vertical Position/Last Pixel + 1 _{IN}: IC70.5 (A4), IC98.12 (2D), J11.10
/Vertical Position/Pixel CLK _{IN}: IC70.6 (A5), J11.11
/Vertical Position/R0: IC60.3 (Q0), IC64.14 (Q0), IC75.3 (Q0), IC79.3 (Q0), IC83.3 (Q0), IC90.3 (Q0), IC95.2 (D0)
/Vertical Position/R1: IC60.5 (Q1), IC64.13 (Q1), IC75.5 (Q1), IC79.5 (Q1), IC83.5 (Q1), IC90.5 (Q1), IC95.3 (D1)
/Vertical Position/R2: IC60.7 (Q2), IC64.12 (Q2), IC75.7 (Q2), IC79.7 (Q2), IC83.7 (Q2), IC90.7 (Q2), IC95.4 (D2)
/Vertical Position/R3: IC60.9 (Q3), IC64.11 (Q3), IC75.9 (Q3), IC79.9 (Q3), IC83.9 (Q3), IC90.9 (Q3), IC95.5 (D3)
/Vertical Position/R4: IC60.12 (Q4), IC65.14 (Q0), IC75.12 (Q4), IC79.12 (Q4), IC83.12 (Q4), IC90.12 (Q4), IC95.6 (D4)
/Vertical Position/R5: IC60.14 (Q5), IC65.13 (Q1), IC75.14 (Q5), IC79.14 (Q5), IC83.14 (Q5), IC90.14 (Q5), IC95.7 (D5)
/Vertical Position/R6: IC60.16 (Q6), IC65.12 (Q2), IC75.16 (Q6), IC79.16 (Q6), IC83.16 (Q6), IC90.16 (Q6), IC95.8 (D6)
/Vertical Position/R7: IC60.18 (Q7), IC65.11 (Q3), IC75.18 (Q7), IC79.18 (Q7), IC83.18 (Q7), IC90.18 (Q7), IC95.9 (D7)
/Vertical Position/R8: IC66.14 (Q0), IC71.1 (1A), IC73.1 (1A), IC77.1 (1A), IC81.1 (1A), IC88.1 (1A), IC96.2 (D0)
/Vertical Position/R9: IC66.13 (Q1), IC71.5 (2A), IC73.5 (2A), IC77.5 (2A), IC81.5 (2A), IC88.5 (2A), IC96.3 (D1)
/Vertical Position/Read Row High: IC97.3 (2A), IC104.6 (2Y)
/Vertical Position/Read Row High ~CS: IC92.10 (~Y5), IC104.4 (2A)
/Vertical Position/Read Row Low: IC95.11 (CP), IC96.11 (CP), IC97.1 (1A), IC104.3 (1Y)
/Vertical Position/Read Row Low ~CS: IC92.11 (~Y4), IC104.1 (1A)
/Vertical Position/Sync Start D0: IC60.2 (P0), IC62.2 (1Q0), IC83.2 (P0), IC84.2 (1Q0)
/Vertical Position/Sync Start D1: IC60.4 (P1), IC62.3 (1Q1), IC83.4 (P1), IC84.3 (1Q1)
/Vertical Position/Sync Start D2: IC60.6 (P2), IC62.5 (1Q2), IC83.6 (P2), IC84.5 (1Q2)
/Vertical Position/Sync Start D3: IC60.8 (P3), IC62.6 (1Q3), IC83.8 (P3), IC84.6 (1Q3)
/Vertical Position/Sync Start D4: IC60.11 (P4), IC62.8 (1Q4), IC83.11 (P4), IC84.8 (1Q4)
/Vertical Position/Sync Start D5: IC60.13 (P5), IC62.9 (1Q5), IC83.13 (P5), IC84.9 (1Q5)
/Vertical Position/Sync Start D6: IC60.15 (P6), IC62.11 (1Q6), IC83.15 (P6), IC84.11 (1Q6)
/Vertical Position/Sync Start D7: IC60.17 (P7), IC62.12 (1Q7), IC83.17 (P7), IC84.12 (1Q7)
/Vertical Position/Sync Start D8: IC62.13 (2Q0), IC71.2 (1B), IC81.2 (1B), IC84.13 (2Q0)
/Vertical Position/Sync Start D9: IC62.14 (2Q1), IC71.6 (2B), IC81.6 (2B), IC84.14 (2Q1)
/Vertical Position/TC_{0123}: IC64.15 (TC), IC65.10 (CET)
/Vertical Position/TC_{4567}: IC65.15 (TC), IC66.10 (CET)
/Vertical Position/Vertical Blank: IC99.5 (1Q), IC107.8 (A7)
/Vertical Position/Vertical Blank _{OUT}: IC107.12 (B7), J12.12
/Vertical Position/Vertical Sync: IC99.9 (2Q), IC100.1 (I1)
/Vertical Position/Vertical Sync _{OUT}: IC107.15 (B4), J12.9
/Vertical Position/Write Back Porch End High: IC84.25 (2LE), IC87.11 (4Y)
/Vertical Position/Write Back Porch End High ~CS: IC85.7 (~Y7), IC87.12 (4A)
/Vertical Position/Write Back Porch End Low: IC84.48 (1LE), IC87.8 (3Y)
/Vertical Position/Write Back Porch End Low ~CS: IC85.9 (~Y6), IC87.9 (3A)
/Vertical Position/Write Back Porch Start High: IC80.25 (2LE), IC87.6 (2Y)
/Vertical Position/Write Back Porch Start High ~CS: IC85.10 (~Y5), IC87.4 (2A)
/Vertical Position/Write Back Porch Start Low: IC80.48 (1LE), IC87.3 (1Y)
/Vertical Position/Write Back Porch Start Low ~CS: IC85.11 (~Y4), IC87.1 (1A)
/Vertical Position/Write Flags: IC102.11 (LE), IC103.11 (4Y)
/Vertical Position/Write Flags ~CS: IC92.12 (~Y3), IC103.12 (4A)
/Vertical Position/Write Front Porch Start High: IC76.25 (2LE), IC86.6 (2Y)
/Vertical Position/Write Front Porch Start High ~CS: IC85.14 (~Y1), IC86.4 (2A)
/Vertical Position/Write Front Porch Start Low: IC76.48 (1LE), IC86.3 (1Y)
/Vertical Position/Write Front Porch Start Low ~CS: IC85.15 (~Y0), IC86.1 (1A)
/Vertical Position/Write Interrupt High: IC91.25 (2LE), IC103.6 (2Y)
/Vertical Position/Write Interrupt High ~CS: IC92.14 (~Y1), IC103.4 (2A)
/Vertical Position/Write Interrupt Low: IC91.48 (1LE), IC103.3 (1Y)
/Vertical Position/Write Interrupt Low ~CS: IC92.15 (~Y0), IC103.1 (1A)
/Vertical Position/Write Sync Start High: IC62.25 (2LE), IC86.11 (4Y)
/Vertical Position/Write Sync Start High ~CS: IC85.12 (~Y3), IC86.12 (4A)
/Vertical Position/Write Sync Start Low: IC62.48 (1LE), IC86.8 (3Y)
/Vertical Position/Write Sync Start Low ~CS: IC85.13 (~Y2), IC86.9 (3A)
/Vertical Position/~Back Porch End: IC64.9 (~PE), IC65.9 (~PE), IC66.9 (~PE), IC67.9 (2Q), IC68.1 (~1RD)
/Vertical Position/~Back Porch End _{CMP}: IC67.12 (2D), IC83.19 (~P=Q)
/Vertical Position/~Back Porch Start: IC67.5 (1Q), IC68.13 (~2RD)
/Vertical Position/~Back Porch Start _{CMP}: IC67.2 (1D), IC79.19 (~P=Q)
/Vertical Position/~Clear Interrupt: IC105.4 (Y), IC106.6 (C)
/Vertical Position/~Front Porch Start: IC61.5 (1Q), IC68.4 (~1SD)
/Vertical Position/~Front Porch Start _{CMP}: IC61.2 (1D), IC75.19 (~P=Q)
/Vertical Position/~Horizontal Sync: IC94.6 (~1Q), IC101.3 (I0)
/Vertical Position/~Interrupt: IC93.5 (1Q), IC107.7 (A6)
/Vertical Position/~Interrupt _{CMP}: IC90.19 (~P=Q), IC93.2 (1D)
/Vertical Position/~Interrupt _{OUT}: IC107.13 (B6), J12.11
/Vertical Position/~Pixel CLK: IC70.13 (B6), IC94.3 (1CP), IC94.11 (2CP), IC98.3 (1CP), IC98.11 (2CP), IC99.3 (1CP), IC99.11 (2CP)
/Vertical Position/~Pixel CLK _{IN}: IC70.7 (A6), J11.12
/Vertical Position/~RD: IC69.1 (DIR), IC70.17 (B2), IC104.2 (1B), IC104.5 (2B), IC104.10 (3B), IC104.13 (4B)
/Vertical Position/~RD_{IN}: IC70.3 (A2), J11.7
/Vertical Position/~Read Row High: IC96.1 (~OE), IC97.4 (2Y)
/Vertical Position/~Read Row Low: IC95.1 (~OE), IC97.6 (1Y)
/Vertical Position/~Reset: IC64.1 (~MR), IC65.1 (~MR), IC66.1 (~MR), IC94.1 (~1RD), IC94.13 (~2RD), IC98.1 (~1RD), IC98.13 (~2RD), IC106.1 (A), J11.14
/Vertical Position/~Sync Start: IC61.9 (2Q), IC68.10 (~2SD)
/Vertical Position/~Sync Start _{CMP}: IC60.19 (~P=Q), IC61.12 (2D)
/Vertical Position/~Vertical Sync: IC99.8 (~2Q), IC100.3 (I0)
/Vertical Position/~WD: IC70.18 (B1), IC86.2 (1B), IC86.5 (2B), IC86.10 (3B), IC86.13 (4B), IC87.2 (1B), IC87.5 (2B), IC87.10 (3B), IC87.13 (4B), IC103.2 (1B), IC103.5 (2B), IC103.10 (3B), IC103.13 (4B)
/Vertical Position/~WD_{IN}: IC70.2 (A1), J11.6
unnamed: IC60.1 (~OE), IC72.4 (Y)
unnamed: IC68.5 (1Q), IC99.2 (1D)
unnamed: IC68.9 (2Q), IC99.12 (2D)
unnamed: IC71.7 (1Y), IC72.1 (B)
unnamed: IC71.3 (2Y), IC72.2 (A)
unnamed: IC73.7 (1Y), IC74.1 (B)
unnamed: IC73.3 (2Y), IC74.2 (A)
unnamed: IC74.4 (Y), IC75.1 (~OE)
unnamed: IC77.7 (1Y), IC78.1 (B)
unnamed: IC77.3 (2Y), IC78.2 (A)
unnamed: IC78.4 (Y), IC79.1 (~OE)
unnamed: IC81.7 (1Y), IC82.1 (B)
unnamed: IC81.3 (2Y), IC82.2 (A)
unnamed: IC82.4 (Y), IC83.1 (~OE)
unnamed: IC88.7 (1Y), IC89.1 (B)
unnamed: IC88.3 (2Y), IC89.2 (A)
unnamed: IC89.4 (Y), IC90.1 (~OE)
unnamed: IC100.6 (S), IC102.18 (Q1)
unnamed: IC100.4 (Y), IC107.5 (A4)
unnamed: IC101.6 (S), IC102.19 (Q0)
unnamed: IC101.4 (Y), IC107.6 (A5)
unnamed: IC93.4 (~1SD), IC106.4 (Y)
